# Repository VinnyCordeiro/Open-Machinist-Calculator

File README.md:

# Open-Machinist-Calculator
Open Machinist Calculator, an open source hardware version of the Machinist Calc™ Pro calculator by Calculated Industries®

### FAQ
* ***Why?***

Because I'm interested in learning machining and that already-available calculator is too expensive for a hobbyist like me. So the idea is research all the formulas, code them in the calculator, and use it when needed.

* ***Why have you chosen the CERN Open Hardware Licence?***

Because as much as I love the GPL, it was created for Open Source **Software**. Open Source Hardware is an entirely different beast, with very different concerns and needs to be attended, there's even an [article](https://www.gnu.org/philosophy/free-hardware-designs.en.html) concerning that on the GNU website.

### TODO
* Start the code for real instead of a place holder. That also means researching all the formulas for each function, both for metric and imperial measurements. That'll be fun. 🙃
* Create a separate repository for the code and license under the GPL v3, the CERN licence is just for the hardware.
* The case is by no means water/dust proof, and that can be a huge problem with metallic dust from machining. That's something that needs improvement.

### UPDATES
November 28th, 2023: Initial public release.

<hr />
<table border="0px">
<th align="left">
&copy; Open Machinist Calculator 2023.
</th>
<tr>
<td>
This documentation describes Open Hardware and is licensed under the CERN Open Hardware Licence version 2 - Strongly Reciprocal.
</td>
</tr>
<tr>
<td>
You may redistribute and modify this documentation under the terms of the
CERN-OHL-S v2. (http://ohwr.org/cernohl). This documentation is distributed
WITHOUT ANY EXPRESS OR IMPLIED WARRANTY, INCLUDING OF
MERCHANTABILITY, SATISFACTORY QUALITY AND FITNESS FOR A
PARTICULAR PURPOSE. Please see the CERN-OHL-S v2 for applicable
conditions.
</td>
</tr>
</table>

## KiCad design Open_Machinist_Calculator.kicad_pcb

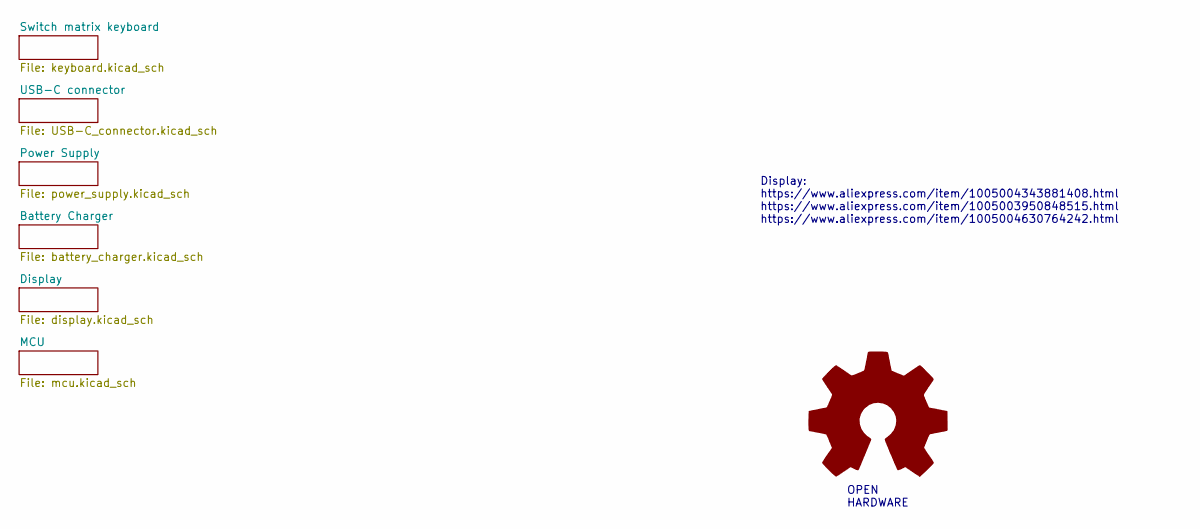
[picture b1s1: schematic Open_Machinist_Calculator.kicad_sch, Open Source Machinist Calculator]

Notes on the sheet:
OPEN HARDWARE
Display: https://www.aliexpress.com/item/1005004343881408.html https://www.aliexpress.com/item/1005003950848515.html https://www.aliexpress.com/item/1005004630764242.html

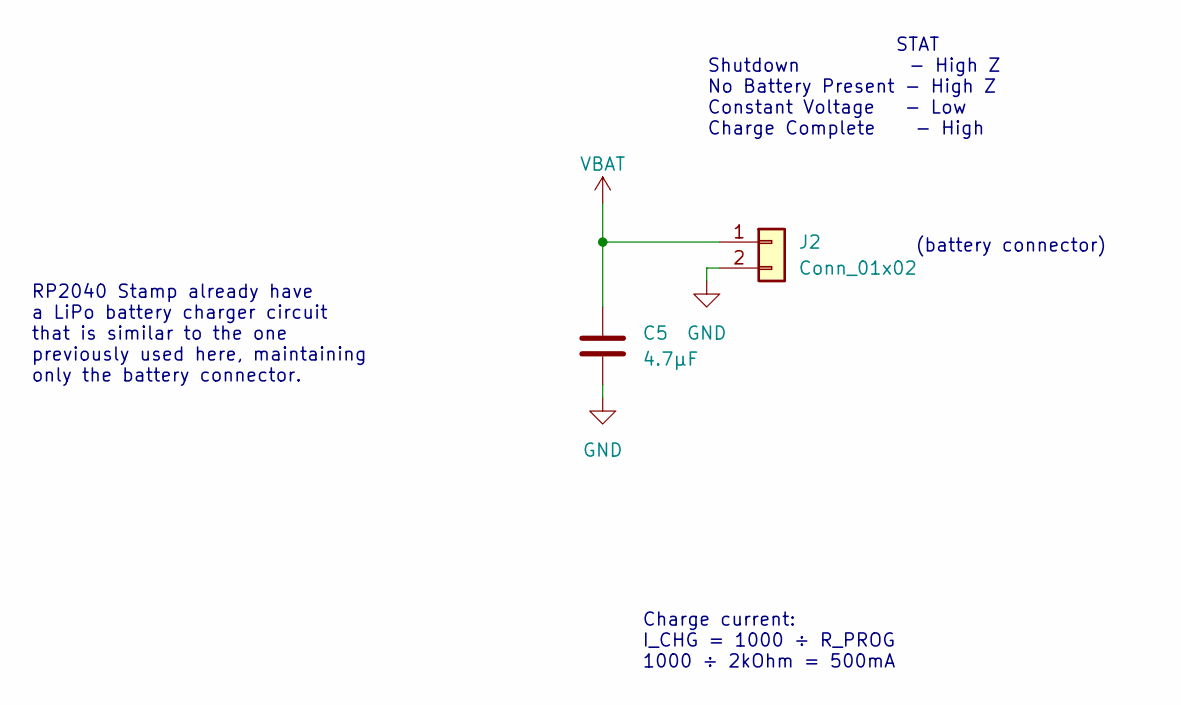
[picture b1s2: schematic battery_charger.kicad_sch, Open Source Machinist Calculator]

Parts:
C5: 4.7µF; C_0805_2012Metric_Pad1.18x1.45mm_HandSolder
J2: Conn_01x02; JST_PH_S2B-PH-K_1x02_P2.00mm_Horizontal

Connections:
GND: C5.2, J2.2; also elsewhere on the board
VBAT: C5.1, J2.1; also elsewhere on the board

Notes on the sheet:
(battery connector)
RP2040 Stamp already have a LiPo battery charger circuit that is similar to the one previously used here, maintaining only the battery connector.
STAT Shutdown - High Z No Battery Present - High Z Constant Voltage - Low Charge Complete - High
Charge current: I_CHG = 1000 ÷ R_PROG 1000 ÷ 2kOhm = 500mA

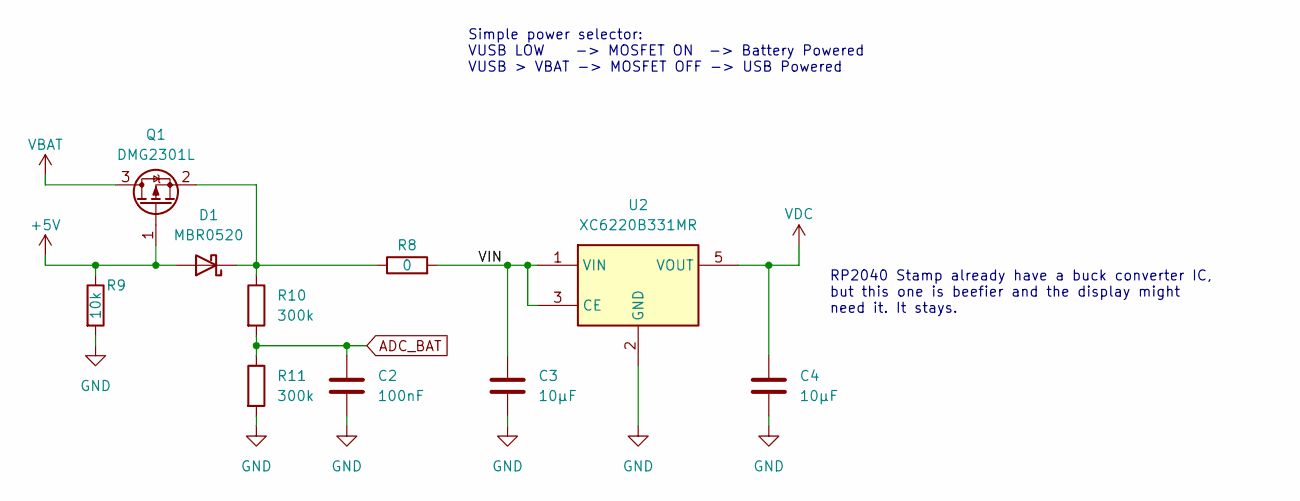
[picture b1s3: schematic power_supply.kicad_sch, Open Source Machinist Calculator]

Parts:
C2: 100nF; C_0805_2012Metric_Pad1.18x1.45mm_HandSolder
C3, C4: 10µF; C_0805_2012Metric_Pad1.18x1.45mm_HandSolder
D1: MBR0520; D_SOD-123
Q1: DMG2301L; SOT-23
R8: 0; R_0805_2012Metric_Pad1.20x1.40mm_HandSolder
R9: 10k; R_0805_2012Metric_Pad1.20x1.40mm_HandSolder
R10, R11: 300k; R_0805_2012Metric_Pad1.20x1.40mm_HandSolder
U2: XC6220B331MR; SOT-23-5

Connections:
+5V: D1.2 (A), Q1.1 (G), R9.1; also elsewhere on the board
/Power Supply/VIN: C3.1, R8.2, U2.1 (VIN), U2.3 (CE)
ADC_BAT: C2.1, R10.2, R11.1; also elsewhere on the board
GND: C2.2, C3.2, C4.2, R9.2, R11.2, U2.2 (GND); also elsewhere on the board
unnamed: D1.1 (K), Q1.2 (S), R8.1, R10.1
VBAT: Q1.3 (D); also elsewhere on the board
VDC: C4.1, U2.5 (VOUT); also elsewhere on the board

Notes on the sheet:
RP2040 Stamp already have a buck converter IC, but this one is beefier and the display might need it. It stays.
Simple power selector: VUSB LOW -> MOSFET ON -> Battery Powered VUSB > VBAT -> MOSFET OFF -> USB Powered

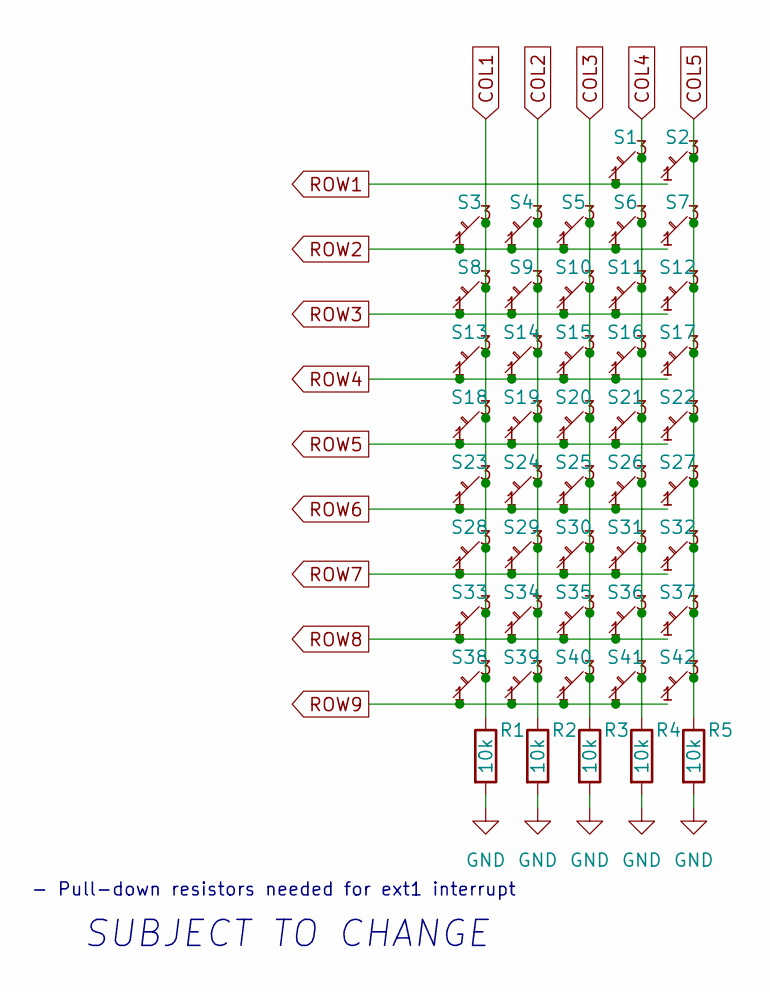
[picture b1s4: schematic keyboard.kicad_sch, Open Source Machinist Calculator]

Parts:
R1, R2, R3, R4, R5: 10k; R_0805_2012Metric_Pad1.20x1.40mm_HandSolder
S1, S2, S3, S4, S5, S6, S7, S8, S9, S10, S11, S12, S13, S14, S15, S16, S17, S18, S19, S20, S21, S22, S23, S24, S25, S26, S27, S28, S29, S30, S31, S32, S33, S34, S35, S36, S37, S38, S39, S40, S41, S42: TL3342

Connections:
COL1: R1.1, S3.3 (Pin2), S3.4 (Pin2), S8.3 (Pin2), S8.4 (Pin2), S13.3 (Pin2), S13.4 (Pin2), S18.3 (Pin2), S18.4 (Pin2), S23.3 (Pin2), S23.4 (Pin2), S28.3 (Pin2), S28.4 (Pin2), S33.3 (Pin2), S33.4 (Pin2), S38.3 (Pin2), S38.4 (Pin2); also elsewhere on the board
COL2: R2.1, S4.3 (Pin2), S4.4 (Pin2), S9.3 (Pin2), S9.4 (Pin2), S14.3 (Pin2), S14.4 (Pin2), S19.3 (Pin2), S19.4 (Pin2), S24.3 (Pin2), S24.4 (Pin2), S29.3 (Pin2), S29.4 (Pin2), S34.3 (Pin2), S34.4 (Pin2), S39.3 (Pin2), S39.4 (Pin2); also elsewhere on the board
COL3: R3.1, S5.3 (Pin2), S5.4 (Pin2), S10.3 (Pin2), S10.4 (Pin2), S15.3 (Pin2), S15.4 (Pin2), S20.3 (Pin2), S20.4 (Pin2), S25.3 (Pin2), S25.4 (Pin2), S30.3 (Pin2), S30.4 (Pin2), S35.3 (Pin2), S35.4 (Pin2), S40.3 (Pin2), S40.4 (Pin2); also elsewhere on the board
COL4: R4.1, S1.3 (Pin2), S1.4 (Pin2), S6.3 (Pin2), S6.4 (Pin2), S11.3 (Pin2), S11.4 (Pin2), S16.3 (Pin2), S16.4 (Pin2), S21.3 (Pin2), S21.4 (Pin2), S26.3 (Pin2), S26.4 (Pin2), S31.3 (Pin2), S31.4 (Pin2), S36.3 (Pin2), S36.4 (Pin2), S41.3 (Pin2), S41.4 (Pin2); also elsewhere on the board
COL5: R5.1, S2.3 (Pin2), S2.4 (Pin2), S7.3 (Pin2), S7.4 (Pin2), S12.3 (Pin2), S12.4 (Pin2), S17.3 (Pin2), S17.4 (Pin2), S22.3 (Pin2), S22.4 (Pin2), S27.3 (Pin2), S27.4 (Pin2), S32.3 (Pin2), S32.4 (Pin2), S37.3 (Pin2), S37.4 (Pin2), S42.3 (Pin2), S42.4 (Pin2); also elsewhere on the board
GND: R1.2, R2.2, R3.2, R4.2, R5.2; also elsewhere on the board
ROW1: S1.1 (Pin1), S1.2 (Pin1), S2.1 (Pin1), S2.2 (Pin1); also elsewhere on the board
ROW2: S3.1 (Pin1), S3.2 (Pin1), S4.1 (Pin1), S4.2 (Pin1), S5.1 (Pin1), S5.2 (Pin1), S6.1 (Pin1), S6.2 (Pin1), S7.1 (Pin1), S7.2 (Pin1); also elsewhere on the board
ROW3: S8.1 (Pin1), S8.2 (Pin1), S9.1 (Pin1), S9.2 (Pin1), S10.1 (Pin1), S10.2 (Pin1), S11.1 (Pin1), S11.2 (Pin1), S12.1 (Pin1), S12.2 (Pin1); also elsewhere on the board
ROW4: S13.1 (Pin1), S13.2 (Pin1), S14.1 (Pin1), S14.2 (Pin1), S15.1 (Pin1), S15.2 (Pin1), S16.1 (Pin1), S16.2 (Pin1), S17.1 (Pin1), S17.2 (Pin1); also elsewhere on the board
ROW5: S18.1 (Pin1), S18.2 (Pin1), S19.1 (Pin1), S19.2 (Pin1), S20.1 (Pin1), S20.2 (Pin1), S21.1 (Pin1), S21.2 (Pin1), S22.1 (Pin1), S22.2 (Pin1); also elsewhere on the board
ROW6: S23.1 (Pin1), S23.2 (Pin1), S24.1 (Pin1), S24.2 (Pin1), S25.1 (Pin1), S25.2 (Pin1), S26.1 (Pin1), S26.2 (Pin1), S27.1 (Pin1), S27.2 (Pin1); also elsewhere on the board
ROW7: S28.1 (Pin1), S28.2 (Pin1), S29.1 (Pin1), S29.2 (Pin1), S30.1 (Pin1), S30.2 (Pin1), S31.1 (Pin1), S31.2 (Pin1), S32.1 (Pin1), S32.2 (Pin1); also elsewhere on the board
ROW8: S33.1 (Pin1), S33.2 (Pin1), S34.1 (Pin1), S34.2 (Pin1), S35.1 (Pin1), S35.2 (Pin1), S36.1 (Pin1), S36.2 (Pin1), S37.1 (Pin1), S37.2 (Pin1); also elsewhere on the board
ROW9: S38.1 (Pin1), S38.2 (Pin1), S39.1 (Pin1), S39.2 (Pin1), S40.1 (Pin1), S40.2 (Pin1), S41.1 (Pin1), S41.2 (Pin1), S42.1 (Pin1), S42.2 (Pin1); also elsewhere on the board

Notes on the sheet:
- Pull-down resistors needed for ext1 interrupt
SUBJECT TO CHANGE

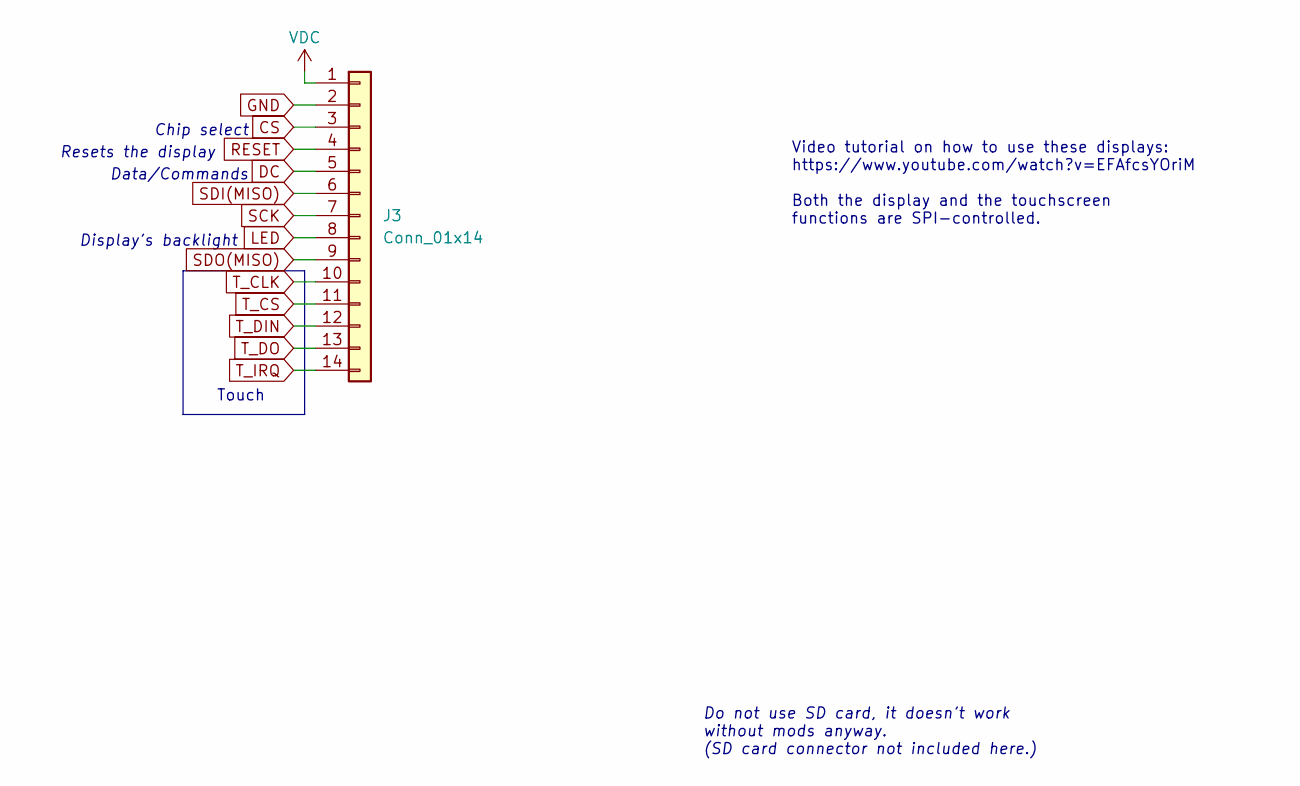
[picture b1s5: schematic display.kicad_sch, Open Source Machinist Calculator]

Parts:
J3: Conn_01x14; PinHeader_1x14_P2.54mm_Vertical

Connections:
CS: J3.3; also elsewhere on the board
DC: J3.5; also elsewhere on the board
GND: J3.2; also elsewhere on the board
LED: J3.8; also elsewhere on the board
RESET: J3.4; also elsewhere on the board
SCK: J3.7; also elsewhere on the board
SDI(MISO): J3.6; also elsewhere on the board
SDO(MISO): J3.9; also elsewhere on the board
T_CLK: J3.10; also elsewhere on the board
T_CS: J3.11; also elsewhere on the board
T_DIN: J3.12; also elsewhere on the board
T_DO: J3.13; also elsewhere on the board
T_IRQ: J3.14; also elsewhere on the board
VDC: J3.1; also elsewhere on the board

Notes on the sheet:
Touch
Video tutorial on how to use these displays: https://www.youtube.com/watch?v=EFAfcsYOriM Both the display and the touchscreen functions are SPI-controlled.
Data/Commands
Resets the display
Display's backlight
Chip select
Do not use SD card, it doesn't work without mods anyway. (SD card connector not included here.)

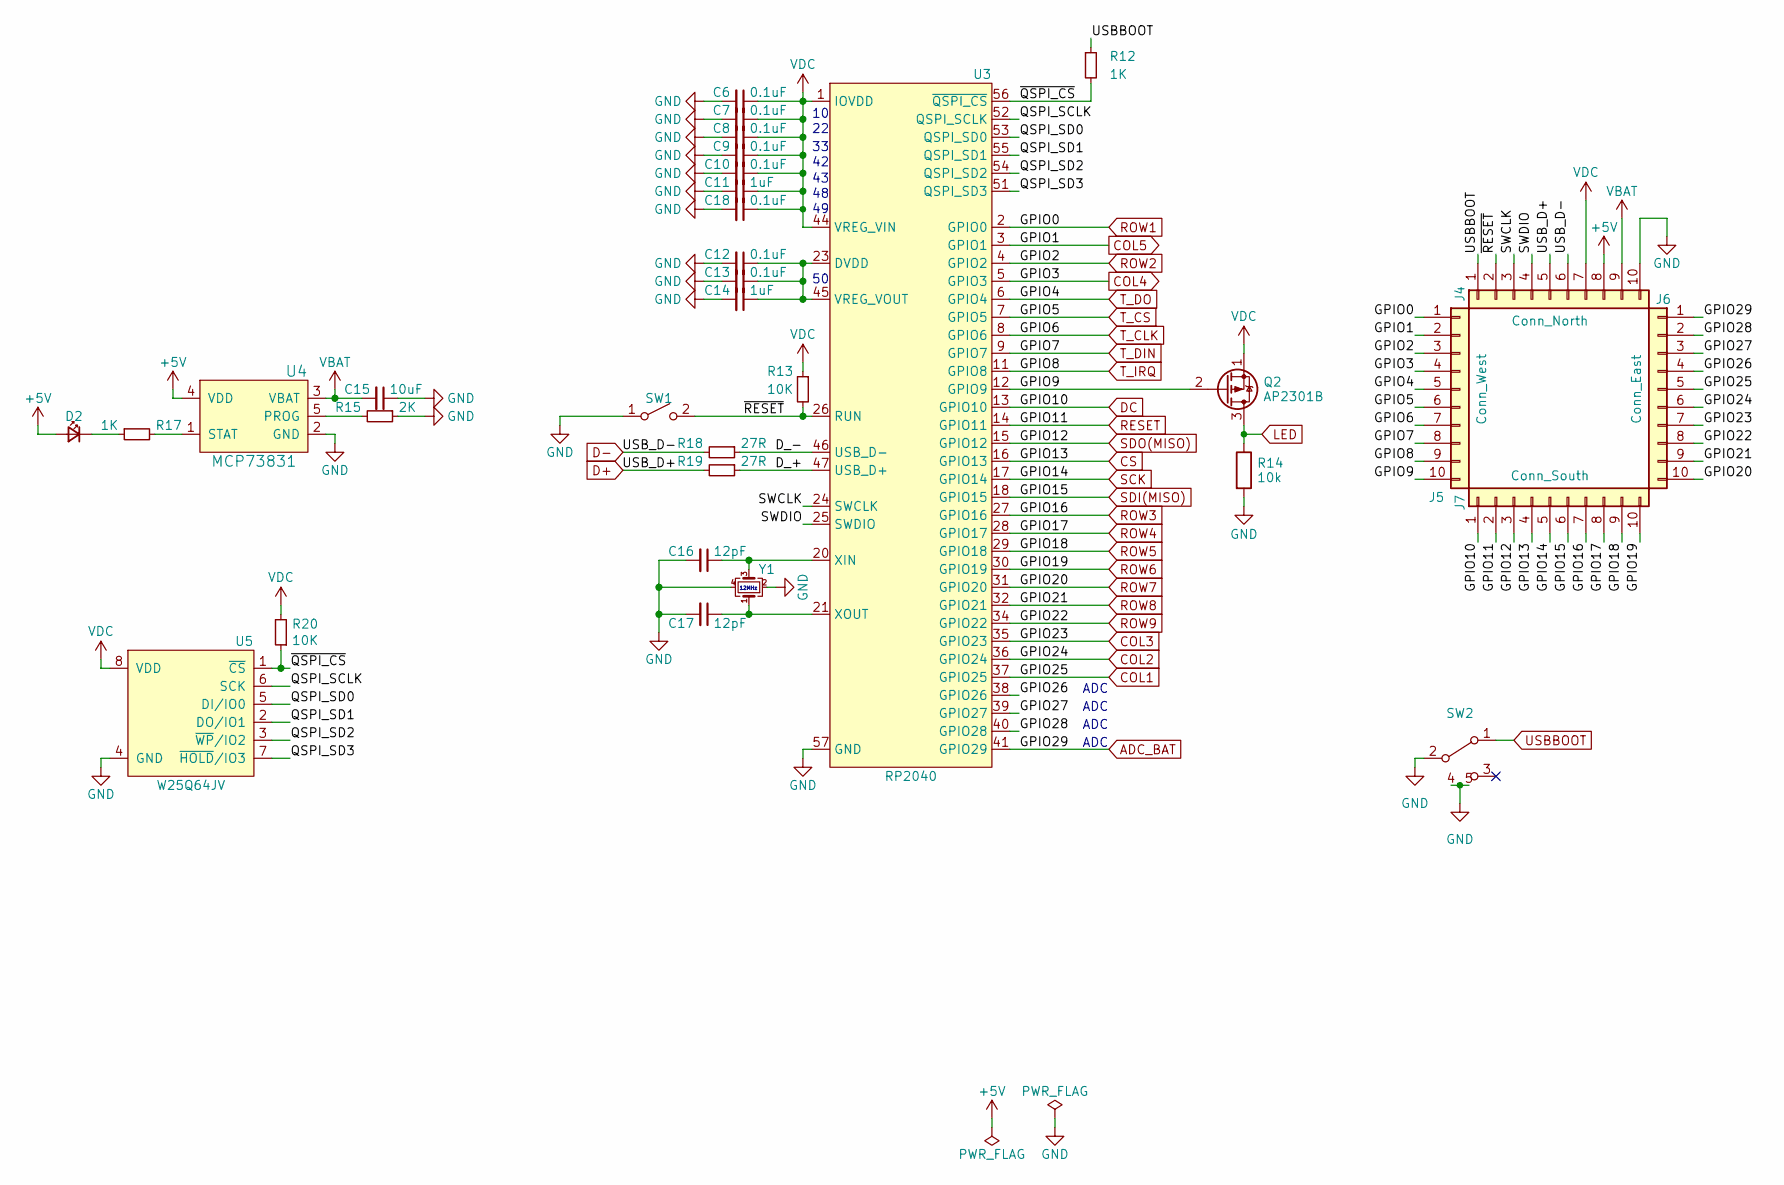
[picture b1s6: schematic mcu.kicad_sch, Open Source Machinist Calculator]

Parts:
C6, C7, C8, C9, C10, C12, C13, C18: 0.1uF; C_0603_1608Metric
C11, C14: 1uF; C_0603_1608Metric
C15: 10uF; C_0603_1608Metric
C16, C17: 12pF; C_0603_1608Metric
D2: LED_CHR; LED_0603_1608Metric
J4: Conn_North; Castellated_1x10_P2.00mm_Vertical
J5: Conn_West; Castellated_1x10_P2.00mm_Vertical
J6: Conn_East; Castellated_1x10_P2.00mm_Vertical
J7: Conn_South; Castellated_1x10_P2.00mm_Vertical
Q2: AP2301B; SOT-23-3; LCSC Part# C2763847
R12, R17: 1K; R_0603_1608Metric
R13, R20: 10K; R_0603_1608Metric
R14: 10k; R_0805_2012Metric_Pad1.20x1.40mm_HandSolder
R15: 2K; R_0603_1608Metric
R18, R19: 27R; R_0603_1608Metric
SW1: SW_RESET; SW_SPST_B3U-1000P
SW2: MK-11C04-G013; LCSC Part# C778185
U3: RP2040; QFN-56_EP_7x7_Pitch0.4mm
U4: MCP73831; SOT-23-5; LCSC C14879
U5: W25Q64JV; WSON-8-1EP_6x5mm_P1.27mm_EP3.4x4mm
Y1: XYDBPCNANF-12MHZ; Crystal_SMD_2520-4Pin_2.5x2.0mm; LCSC C521567

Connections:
+5V: D2.2 (A), J4.8, U4.4 (VDD); also elsewhere on the board
/MCU/D_+: R19.1, U3.47 (USB_D+)
/MCU/D_-: R18.1, U3.46 (USB_D-)
/MCU/GPIO9: J5.10, Q2.2 (G), U3.12 (GPIO9)
/MCU/GPIO26: J6.4, U3.38 (GPIO26)
/MCU/GPIO27: J6.3, U3.39 (GPIO27)
/MCU/GPIO28: J6.2, U3.40 (GPIO28)
/MCU/QSPI_SCLK: U3.52 (QSPI_SCLK), U5.6 (SCK)
/MCU/QSPI_SD0: U3.53 (QSPI_SD0), U5.5 (DI/IO0)
/MCU/QSPI_SD1: U3.55 (QSPI_SD1), U5.2 (DO/IO1)
/MCU/QSPI_SD2: U3.54 (QSPI_SD2), U5.3 (~WP/IO2)
/MCU/QSPI_SD3: U3.51 (QSPI_SD3), U5.7 (~HOLD/IO3)
/MCU/SWCLK: J4.3, U3.24 (SWCLK)
/MCU/SWDIO: J4.4, U3.25 (SWDIO)
/MCU/~QSPI_CS: R12.2, R20.1, U3.56 (~QSPI_CS), U5.1 (~CS)
/MCU/~RESET: J4.2, R13.2, SW1.2 (B), U3.26 (RUN)
ADC_BAT: J6.1, U3.41 (GPIO29); also elsewhere on the board
COL1: J6.5, U3.37 (GPIO25); also elsewhere on the board
COL2: J6.6, U3.36 (GPIO24); also elsewhere on the board
COL3: J6.7, U3.35 (GPIO23); also elsewhere on the board
COL4: J5.4, U3.5 (GPIO3); also elsewhere on the board
COL5: J5.2, U3.3 (GPIO1); also elsewhere on the board
CS: J7.4, U3.16 (GPIO13); also elsewhere on the board
D+: J4.5, R19.2; also elsewhere on the board
D-: J4.6, R18.2; also elsewhere on the board
DC: J7.1, U3.13 (GPIO10); also elsewhere on the board
GND: C6.2, C7.2, C8.2, C9.2, C10.2, C11.2, C12.2, C13.2, C14.2, C15.1, C16.2, C17.2, C18.2, J4.10, R14.2, R15.1, SW1.1 (A), SW2.2 (B), SW2.4, SW2.5 (4), U3.19 (TESTEN), U3.57 (GND), U4.2 (GND), U5.4 (GND), U5.9 (GND), Y1.2, Y1.4; also elsewhere on the board
LED: Q2.3 (D), R14.1; also elsewhere on the board
unnamed: D2.1 (K), R17.1
unnamed: C12.1, C13.1, C14.1, U3.23 (DVDD), U3.45 (VREG_VOUT), U3.50 (DVDD)
unnamed: C16.1, U3.20 (XIN), Y1.3
unnamed: C17.1, U3.21 (XOUT), Y1.1
unnamed: R15.2, U4.5 (PROG)
unnamed: R17.2, U4.1 (STAT)
RESET: J7.2, U3.14 (GPIO11); also elsewhere on the board
ROW1: J5.1, U3.2 (GPIO0); also elsewhere on the board
ROW2: J5.3, U3.4 (GPIO2); also elsewhere on the board
ROW3: J7.7, U3.27 (GPIO16); also elsewhere on the board
ROW4: J7.8, U3.28 (GPIO17); also elsewhere on the board
ROW5: J7.9, U3.29 (GPIO18); also elsewhere on the board
ROW6: J7.10, U3.30 (GPIO19); also elsewhere on the board
ROW7: J6.10, U3.31 (GPIO20); also elsewhere on the board
ROW8: J6.9, U3.32 (GPIO21); also elsewhere on the board
ROW9: J6.8, U3.34 (GPIO22); also elsewhere on the board
SCK: J7.5, U3.17 (GPIO14); also elsewhere on the board
SDI(MISO): J7.6, U3.18 (GPIO15); also elsewhere on the board
SDO(MISO): J7.3, U3.15 (GPIO12); also elsewhere on the board
T_CLK: J5.7, U3.8 (GPIO6); also elsewhere on the board
T_CS: J5.6, U3.7 (GPIO5); also elsewhere on the board
T_DIN: J5.8, U3.9 (GPIO7); also elsewhere on the board
T_DO: J5.5, U3.6 (GPIO4); also elsewhere on the board
T_IRQ: J5.9, U3.11 (GPIO8); also elsewhere on the board
USBBOOT: J4.1, R12.1, SW2.1 (A)
VBAT: C15.2, J4.9, U4.3 (VBAT); also elsewhere on the board
VDC: C6.1, C7.1, C8.1, C9.1, C10.1, C11.1, C18.1, J4.7, Q2.1 (S), R13.1, R20.2, U3.1 (IOVDD), U3.10 (IOVDD), U3.22 (IOVDD), U3.33 (IOVDD), U3.42 (IOVDD), U3.43 (ADC_AVDD), U3.44 (VREG_VIN), U3.48 (USB_VDD), U3.49 (IOVDD), U5.8 (VDD); also elsewhere on the board

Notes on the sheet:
ADC
12MHz

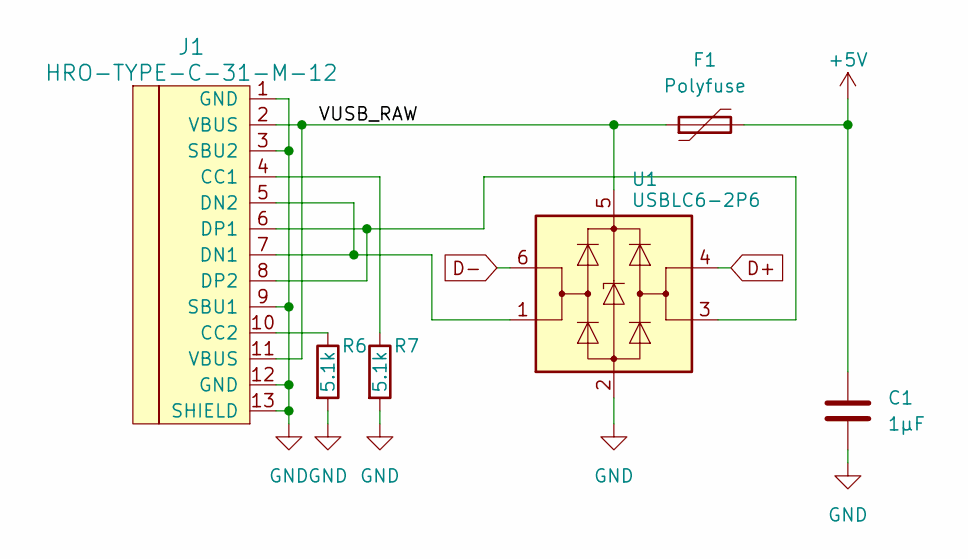
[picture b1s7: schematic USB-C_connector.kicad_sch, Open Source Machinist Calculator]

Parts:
C1: 1µF; C_0805_2012Metric_Pad1.18x1.45mm_HandSolder
F1: Polyfuse; R_1206_3216Metric_Pad1.30x1.75mm_HandSolder
J1: HRO-TYPE-C-31-M-12; HRO-TYPE-C-31-M-12-HandSoldering
R6, R7: 5.1k; R_0805_2012Metric_Pad1.20x1.40mm_HandSolder
U1: USBLC6-2P6; SOT-666

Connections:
+5V: C1.1, F1.2; also elsewhere on the board
/USB-C connector/VUSB_RAW: F1.1, J1.2 (VBUS), J1.11 (VBUS), U1.5 (VBUS)
D+: U1.4 (I/O2); also elsewhere on the board
D-: U1.6 (I/O1); also elsewhere on the board
GND: C1.2, J1.1 (GND), J1.3 (SBU2), J1.9 (SBU1), J1.12 (GND), J1.13 (SHIELD), R6.2, R7.2, U1.2 (GND); also elsewhere on the board
unnamed: J1.4 (CC1), R7.1
unnamed: J1.10 (CC2), R6.1
unnamed: J1.5 (DN2), J1.7 (DN1), U1.1 (I/O1)
unnamed: J1.6 (DP1), J1.8 (DP2), U1.3 (I/O2)

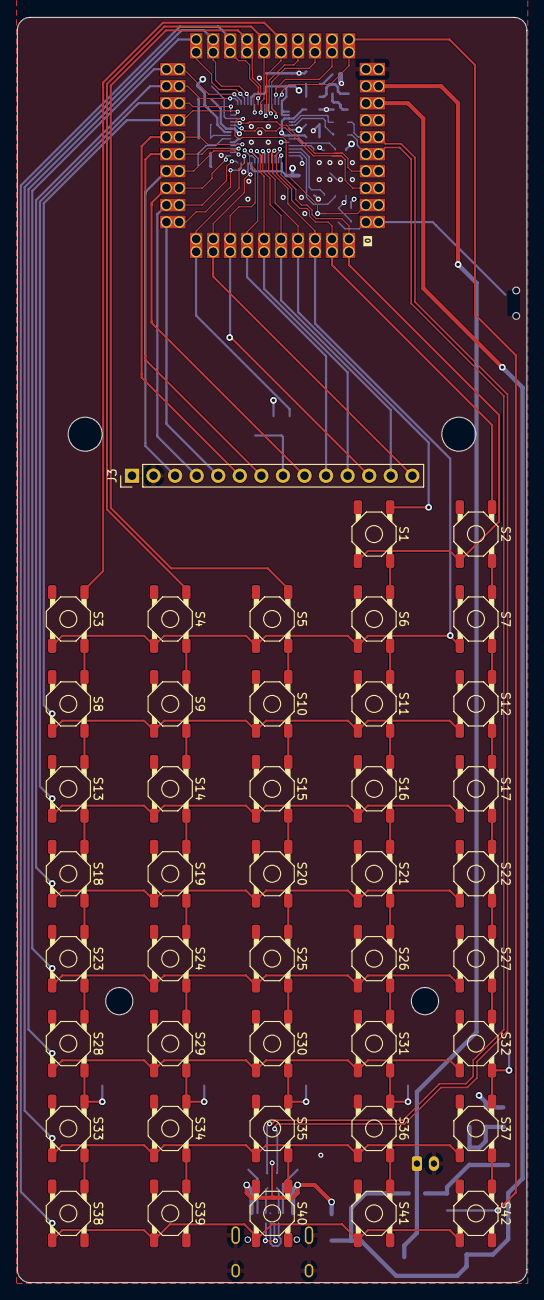
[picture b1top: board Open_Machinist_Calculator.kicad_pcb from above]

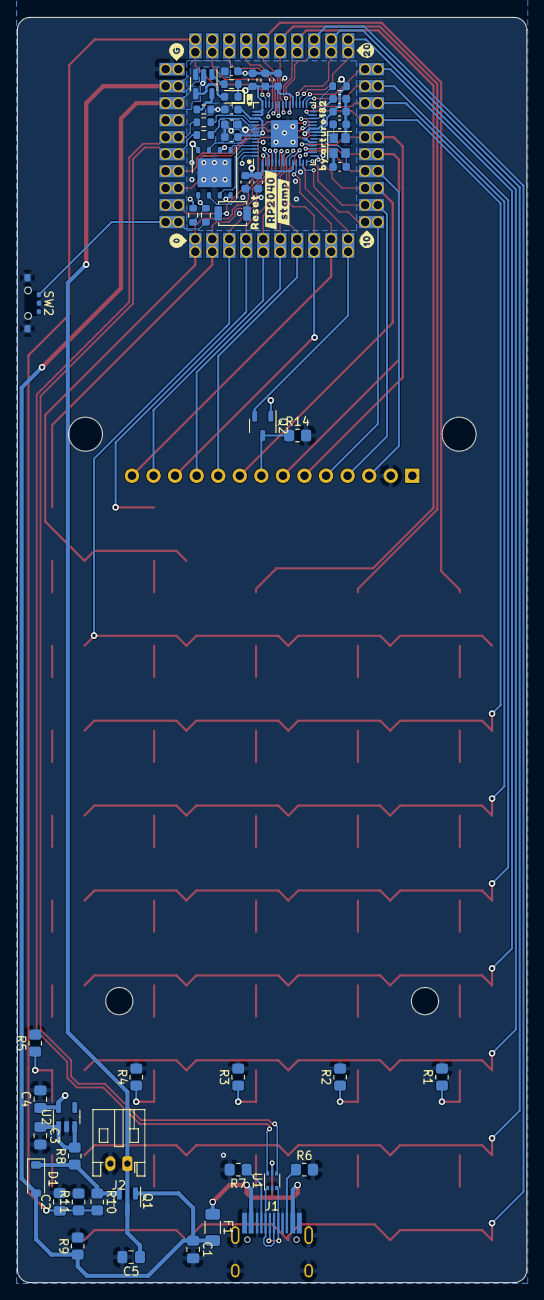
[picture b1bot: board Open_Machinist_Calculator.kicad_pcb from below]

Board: 4 copper layers, 60.0 x 149.0 mm, 99 parts (56 on the bottom side), 62 nets.

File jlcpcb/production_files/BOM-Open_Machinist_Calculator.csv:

Comment,Designator,Footprint,LCSC
0.1uF,"C10,C12,C13,C18,C6,C7,C8,C9",C_0603_1608Metric,C14663
MCP73831,U4,SOT-23-5,C14879
1uF,"C11,C14",C_0603_1608Metric,C15849
10µF,"C3,C4",C_0805_2012Metric_Pad1.18x1.45mm_HandSolder,C15850
HRO-TYPE-C-31-M-12,J1,HRO-TYPE-C-31-M-12-HandSoldering,C165948
10k,"R1,R14,R2,R3,R4,R5,R9",R_0805_2012Metric_Pad1.20x1.40mm_HandSolder,C17414
0,R8,R_0805_2012Metric_Pad1.20x1.40mm_HandSolder,C17477
300k,"R10,R11",R_0805_2012Metric_Pad1.20x1.40mm_HandSolder,C17616
4.7µF,C5,C_0805_2012Metric_Pad1.18x1.45mm_HandSolder,C1779
10uF,C15,C_0603_1608Metric,C19702
RP2040,U3,QFN-56_EP_7x7_Pitch0.4mm,C2040
1K,"R12,R17",R_0603_1608Metric,C21190
LED_CHR,D2,LED_0603_1608Metric,C2286
2K,R15,R_0603_1608Metric,C22975
SW_RESET,SW1,SW_SPST_B3U-1000P,C231329
27R,"R18,R19",R_0603_1608Metric,C25190
10K,"R13,R20",R_0603_1608Metric,C25804
AP2301B,Q2,SOT-23-3,C2763847
5.1k,"R6,R7",R_0805_2012Metric_Pad1.20x1.40mm_HandSolder,C27834
USBLC6-2P6,U1,SOT-666,C2827693
1µF,C1,C_0805_2012Metric_Pad1.18x1.45mm_HandSolder,C28323
~,"S1,S10,S11,S12,S13,S14,S15,S16,S17,S18,S19,S2,S20,S21,S22,S23,S24,S25,S26,S27,S28,S29,S3,S30,S31,S32,S33,S34,S35,S36,S37,S38,S39,S4,S40,S41,S42,S5,S6,S7,S8,S9",TL3342,C2886898
W25Q64JV,U5,WSON-8-1EP_6x5mm_P1.27mm_EP3.4x4mm,C2940197
XC6220B331MR,U2,SOT-23-5,C3040644
12pF,"C16,C17",C_0603_1608Metric,C38523
100nF,C2,C_0805_2012Metric_Pad1.18x1.45mm_HandSolder,C49678
DMG2301L,Q1,SOT-23,C508195
XYDBPCNANF-12MHZ,Y1,Crystal_SMD_2520-4Pin_2.5x2.0mm,C521567
MBR0520,D1,D_SOD-123,C77335
MK-11C04-G013,SW2,MK-11C04-G013,C778185
Polyfuse,F1,R_1206_3216Metric_Pad1.30x1.75mm_HandSolder,C910830
Conn_North,J4,Castellated_1x10_P2.00mm_Vertical,
Conn_01x02,J2,JST_PH_S2B-PH-K_1x02_P2.00mm_Horizontal,
Conn_01x14,J3,PinHeader_1x14_P2.54mm_Vertical,
Conn_South,J7,Castellated_1x10_P2.00mm_Vertical,
Conn_East,J6,Castellated_1x10_P2.00mm_Vertical,
Conn_West,J5,Castellated_1x10_P2.00mm_Vertical,

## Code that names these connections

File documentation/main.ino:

/* 
 * Open Source Machinist Calculator
 * (Based on Arduino Keypad calculator Program: https://projecthub.arduino.cc/123samridhgarg/arduino-calculator-bce0df)
 */

#include "SPI.h"
#include "Adafruit_GFX.h"
#include "Adafruit_ILI9341.h"
#include <Keypad.h> //Header file for Keypad from https://github.com/Chris--A/Keypad

const byte ROWS = 9;
const byte COLS = 5;

// Define  the Keymap
char keys[ROWS][COLS] = {

  {     '',    '',        '',         'Off',        'On/C'},
  {   'Vc',   'n',      'Vf','Bolt_Pattern', 'Thread_Size'},
  {    'z',  'fz',      'fn',    'Diameter',  'Drill_Size'},
  {    'x',   'y',       'r',       'Angle',           '%'},
  {   'mm','inch','Fraction',        'mils',   'Backspace'},
  { 'Conv',   '7',       '8',           '9',      'Divide'},
  { 'Stor',   '4',       '5',           '6',    'Multiply'},
  {  'Rcl',   '1',       '2',           '3', 'Subtraction'},
  {   'M+',   '0',     'Dot',       'Equal',    'Addition'}

};

// Everything from here is unedited from the example.

byte rowPins[ROWS]  = { 0, 1, 2, 3 };// Connect keypad ROW0, ROW1, ROW2 and ROW3 to these Arduino pins.
byte  colPins[COLS] = { 4, 5, 6, 7 }; // Connect keypad COL0, COL1 and COL2 to these Arduino  pins.

Keypad kpd = Keypad( makeKeymap(keys), rowPins, colPins, ROWS, COLS  ); //  Create the Keypad

const int rs = 8, en = 9, d4 = 10, d5 = 11, d6 =  12, d7 = 13; //Pins to which LCD is connected
LiquidCrystal lcd(rs, en, d4, d5,  d6, d7);

 long Num1,Num2,Number;
 char key,action;
 boolean result  = false;
 
void setup() {
  lcd.begin(16, 2); //We are using a 16*2 LCD  display
  lcd.print("DIY Calculator"); //Display a intro message
  lcd.setCursor(0,  1);   // set the cursor to column 0, line 1
  lcd.print("-CircuitDigest");  //Display a intro message 

   delay(2000); //Wait for display to show info
    lcd.clear(); //Then clean it
}

void loop() {
  
key = kpd.getKey();  //storing pressed key value in a char

if (key!=NO_KEY)
DetectButtons();

if  (result==true)
CalculateResult();

DisplayResult();   
}

void  DetectButtons()
{ 
     lcd.clear(); //Then clean it
    if (key=='*')  //If cancel Button is pressed
    {Serial.println ("Button Cancel"); Number=Num1=Num2=0;  result=false;}
    
     if (key == '1') //If Button 1 is pressed
    {Serial.println  ("Button 1"); 
    if (Number==0)
    Number=1;
    else
    Number  = (Number*10) + 1; //Pressed twice
    }
    
     if (key == '4') //If  Button 4 is pressed
    {Serial.println ("Button 4"); 
    if (Number==0)
    Number=4;
    else
    Number = (Number*10) + 4; //Pressed twice
    }
    
     if (key == '7') //If Button 7 is pressed
    {Serial.println ("Button  7");
    if (Number==0)
    Number=7;
    else
    Number = (Number*10)  + 7; //Pressed twice
    } 
  

    if (key == '0')
    {Serial.println  ("Button 0"); //Button 0 is Pressed
    if (Number==0)
    Number=0;
    else
    Number = (Number*10) + 0; //Pressed twice
    }
    
     if  (key == '2') //Button 2 is Pressed
    {Serial.println ("Button 2"); 
     if  (Number==0)
    Number=2;
    else
    Number = (Number*10) + 2; //Pressed  twice
    }
    
     if (key == '5')
    {Serial.println ("Button  5"); 
     if (Number==0)
    Number=5;
    else
    Number = (Number*10)  + 5; //Pressed twice
    }
    
     if (key == '8')
    {Serial.println  ("Button 8"); 
     if (Number==0)
    Number=8;
    else
    Number  = (Number*10) + 8; //Pressed twice
    }   
  

    if (key == '#')
    {Serial.println ("Button Equal"); 
    Num2=Number;
    result = true;
    }
    
     if (key == '3')
    {Serial.println ("Button 3"); 
     if (Number==0)
    Number=3;
    else
    Number = (Number*10) + 3;  //Pressed twice
    }
    
     if (key == '6')
    {Serial.println  ("Button 6"); 
    if (Number==0)
    Number=6;
    else
    Number  = (Number*10) + 6; //Pressed twice
    }
    
     if (key == '9')
    {Serial.println ("Button 9");
    if (Number==0)
    Number=9;
    else
    Number = (Number*10) + 9; //Pressed twice
    }  

      if (key ==  'A' || key == 'B' || key == 'C' || key == 'D') //Detecting Buttons on Column 4
  {
    Num1 = Number;    
    Number =0;
    if (key == 'A')
    {Serial.println  ("Addition"); action = '+';}
     if (key == 'B')
    {Serial.println ("Subtraction");  action = '-'; }
     if (key == 'C')
    {Serial.println ("Multiplication");  action = '*';}
     if (key == 'D')
    {Serial.println ("Devesion"); action  = '/';}  

    delay(100);
  }
  
}

void CalculateResult()
{
  if (action=='+')
    Number = Num1+Num2;

  if (action=='-')
    Number  = Num1-Num2;

  if (action=='*')
    Number = Num1*Num2;

  if (action=='/')
    Number = Num1/Num2; 
}

void DisplayResult()
{
  lcd.setCursor(0,  0);   // set the cursor to column 0, line 1
  lcd.print(Num1); lcd.print(action);  lcd.print(Num2); 
  
  if (result==true)
  {lcd.print(" ="); lcd.print(Number);}  //Display the result
  
  lcd.setCursor(0, 1);   // set the cursor to column  0, line 1
  lcd.print(Number); //Display the result
}

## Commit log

2023-11-28 Initial upload
    Hardware is almost done: PCB is done, first version of the case is done but needs improvements for at least dust protection. Software needs to be written, there are just some example codes found on t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
2023-11-28 Upload of license files
    Files concerning the CERN Open Hardware Licence Version 2 - Strongly Reciprocal. Includes user guide.
2023-11-28 Update README.md
    Concerning the licensing of the future code.
2023-11-28 Update README.md
    Deleted a part that should have been deleted earlier. The perks of copying/pasting...

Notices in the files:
mcu.kicad_sch:
Licensed under the CERN Open Hardware Licence v1.2
